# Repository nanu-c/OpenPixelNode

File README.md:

OpenPixelNode
=============

This project includes both hardware and software for an open-source LED controller for up to 4 ArtNet universes.

More images here: http://flic.kr/s/aHsjQY2NrD

Hardware
--------
The hardware design is Arduino-compatible in terms of being based on an ATmega328 microcontroller running at 16MHz.
It uses the Wiznet Wiz820io addon board for Ethernet communication. There are voltage regulators for both 5V and 3.3V for the two logic circuits. This allows the board to be supplied with voltages of 5V to 30V.
There are 4 LED outputs with two digital ports each. This allows the board to control either SPI or single-wire LED strips.
At the moment there is only ICSP headers for programming.

Software
--------
The software is an Arduino sketch using a library for the ArtNet protocol and whatever LED communication protocol you may want to use. Please update the FastLED controller type to whatever LED you are using.

Dependencies
------------
[Arduino_ArtNet](https://github.com/media-architecture/Arduino_ArtNet)

[FastLED](https://github.com/media-architecture/FastLED)

[WIZ_Ethernet_Library](https://github.com/media-architecture/WIZ_Ethernet_Library)

[TrueRandom](https://code.google.com/p/tinkerit/wiki/TrueRandom)

Version history
---------------

### Prototype 2 (January 2014)
### Prototype 1 (September 2013)

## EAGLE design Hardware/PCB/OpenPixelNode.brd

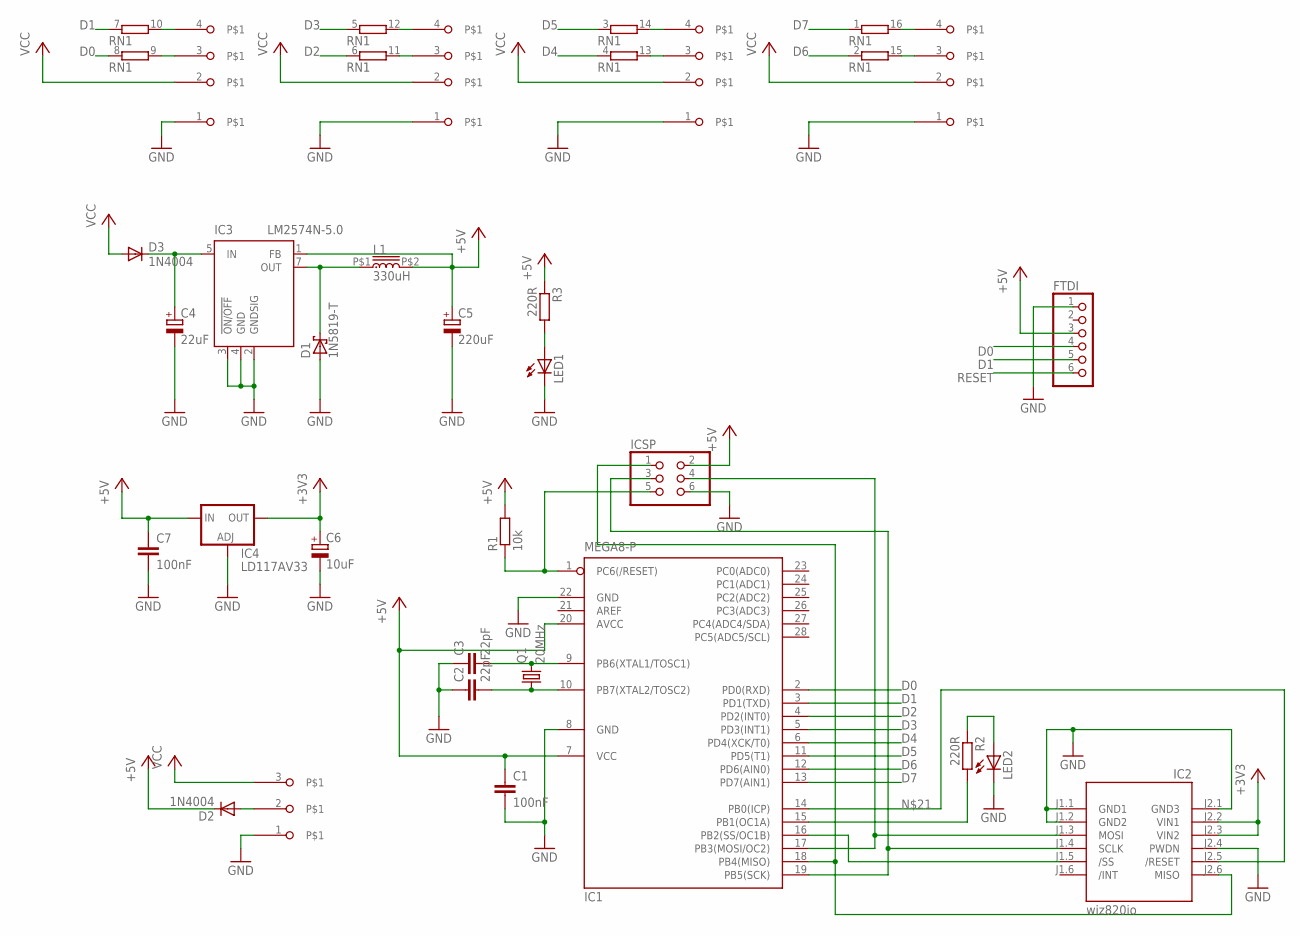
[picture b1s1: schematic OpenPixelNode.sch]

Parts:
C1, C7: 100nF; C025-025X050
C2, C3: 22pF; C025-025X050
C4: 22uF; E2,5-6
C5: 220uF; E2,5-6
C6: 10uF; E2,5-6
D1: 1N5819-T; DO41-7.6
D2, D3: 1N4004; DO41-10
FTDI: PINHD-1X6; 1X06
IC1: MEGA8-P; DIL28-3
IC2: wiz820io; WIZ820IO
IC3: LM2574N-5.0; DIL08
IC4: LD117AV33; TO220L1
ICSP: PINHD-2X3; 2X03
L1: 330uH; 13R334C
LED1, LED2: LED3MM
Q1: 20MHz; HC49/S
R1: 10k; 0207/10
R2, R3: 220R; 0207/10
RN1: 8R-P; DIL16
U$1, U$2, U$3, U$4: 691322110004
U$5: CTB9358/3

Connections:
+3V3: C6.+, IC2.J2.2 (VIN1), IC2.J2.3 (VIN2), IC4.2 (OUT)
+5V: C1.1, C5.+, C7.1, D2.C, FTDI.3, IC1.7 (VCC), IC1.20 (AVCC), IC3.1 (FB), IC4.3 (IN), ICSP.2, L1.P$2 (2), R1.2, R3.1; also elsewhere on the board
D0: FTDI.4, IC1.2 (PD0(RXD)), RN1.8 (1); also elsewhere on the board
D1: FTDI.5, IC1.3 (PD1(TXD)), RN1.7 (1); also elsewhere on the board
D2: IC1.4 (PD2(INT0)), RN1.6 (1)
D3: IC1.5 (PD3(INT1)), RN1.5 (1)
D4: IC1.6 (PD4(XCK/T0)), RN1.4 (1)
D5: IC1.11 (PD5(T1)), RN1.3 (1)
D6: IC1.12 (PD6(AIN0)), RN1.2 (1)
D7: IC1.13 (PD7(AIN1)), RN1.1
GND: C1.2, C2.1, C3.1, C4.-, C5.-, C6.-, C7.2, D1.A, FTDI.1, IC1.8 (GND), IC1.22 (GND), IC2.J1.1 (GND1), IC2.J1.2 (GND2), IC2.J2.1 (GND3), IC2.J2.4 (PWDN), IC3.2 (GNDSIG), IC3.3 (!ON/OFF), IC3.4 (GND), IC4.1 (ADJ), ICSP.6, LED1.K (C), LED2.K (C), U$1.1, U$2.1, U$3.1, U$4.1, U$5.1; also elsewhere on the board
unnamed: LED1.A, R3.2
unnamed: C3.2, IC1.9 (PB6(XTAL1/TOSC1)), Q1.2
unnamed: C2.2, IC1.10 (PB7(XTAL2/TOSC2)), Q1.1
unnamed: IC1.16 (PB2(SS/OC1B)), IC2.J1.5 (/SS)
unnamed: IC1.18 (PB4(MISO)), IC2.J2.6 (MISO), ICSP.1
unnamed: D2.A, U$5.2
unnamed: IC1.17 (PB3(MOSI/OC2)), IC2.J1.3 (MOSI), ICSP.4
unnamed: LED2.A, R2.1
unnamed: C4.+, D3.C, IC3.5 (IN)
unnamed: D1.C, IC3.7 (OUT), L1.P$1 (1)
unnamed: RN1.11 (2), U$2.3
unnamed: RN1.12 (2), U$2.4
unnamed: RN1.13 (2), U$3.3
unnamed: RN1.14 (2), U$3.4
unnamed: RN1.15 (2), U$4.3
unnamed: RN1.16 (2), U$4.4
unnamed: RN1.10 (2), U$1.4
unnamed: RN1.9 (2), U$1.3
unnamed: IC1.14 (PB0(ICP)), IC2.J2.5 (/RESET)
unnamed: IC1.15 (PB1(OC1A)), R2.2
RESET: FTDI.6, IC1.1 (PC6(/RESET)), ICSP.5, R1.1; also elsewhere on the board
SCK: IC1.19 (PB5(SCK)), IC2.J1.4 (SCLK), ICSP.3
VCC: D3.A, U$1.2, U$2.2, U$3.2, U$4.2, U$5.3

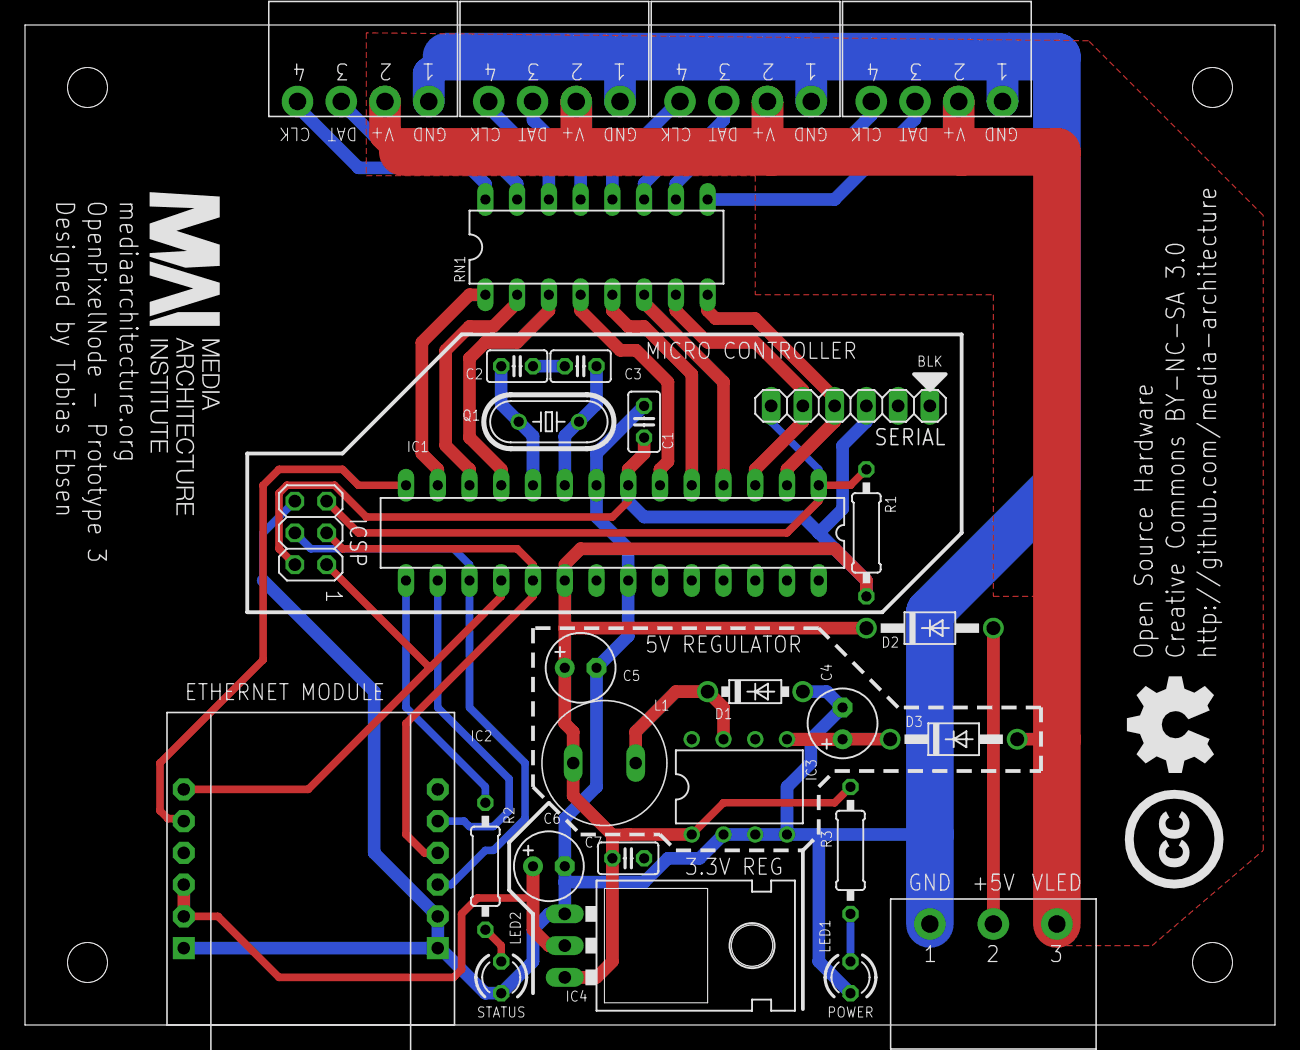
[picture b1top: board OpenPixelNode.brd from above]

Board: 2 copper layers, 100.0 x 80.0 mm, 29 parts (0 on the bottom side), 34 nets.

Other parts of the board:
SERIAL: 1X06

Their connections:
+5V: SERIAL.3; also elsewhere on the board
D0: SERIAL.4; also elsewhere on the board
D1: SERIAL.5; also elsewhere on the board
GND: SERIAL.1; also elsewhere on the board
RESET: SERIAL.6; also elsewhere on the board

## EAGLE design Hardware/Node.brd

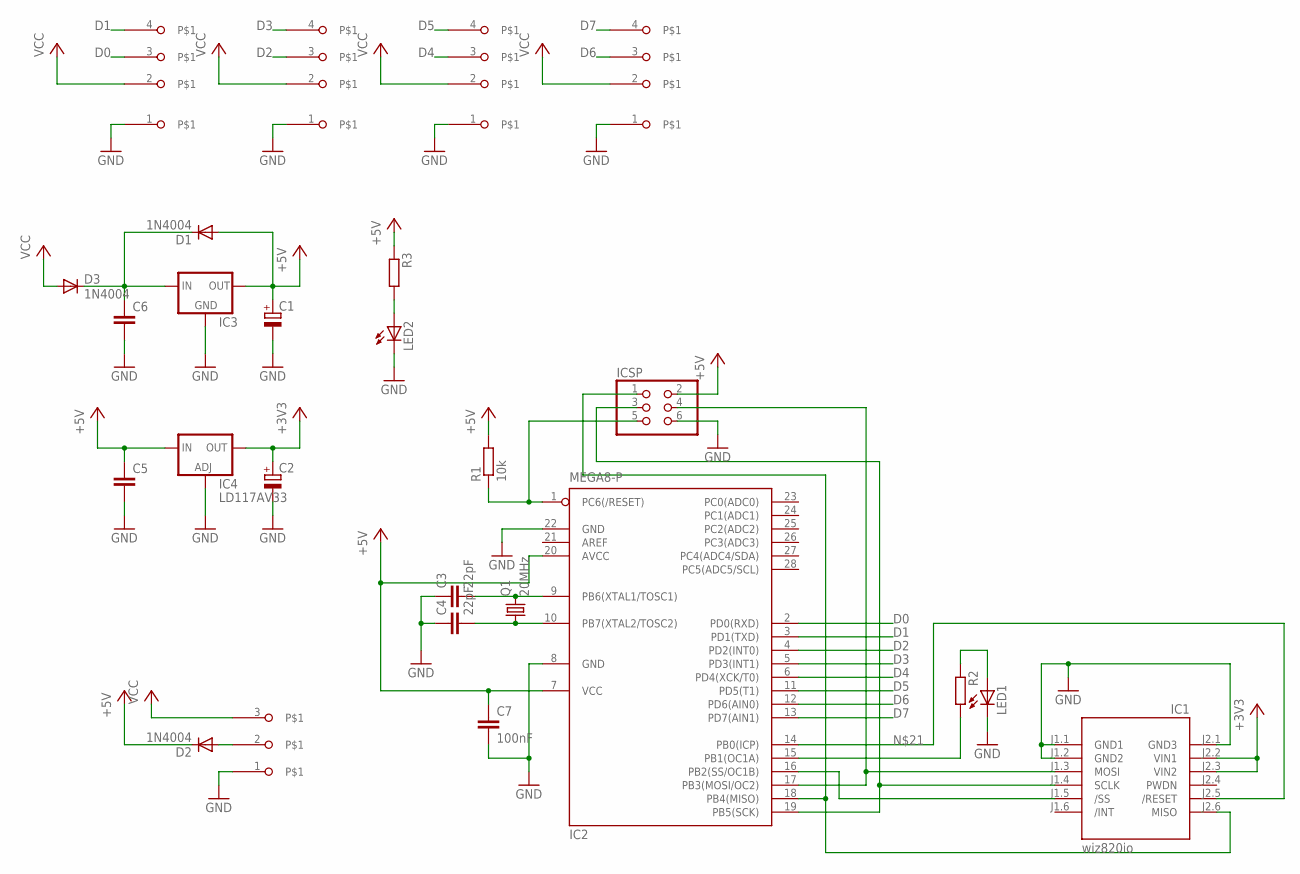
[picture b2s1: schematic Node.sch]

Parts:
C1: CPOL-EUE5-10.5; E5-10,5
C2: CPOL-EUE2.5-6; E2,5-6
C3, C4: 22pF; C025-025X050
C5, C6: C-EU025-025X050; C025-025X050
C7: 100nF; C025-025X050
D1, D2, D3: 1N4004; DO41-10
IC1: wiz820io; WIZ820IO
IC2: MEGA8-P; DIL28-3
IC3: 78XXL
IC4: LD117AV33; TO220L1
ICSP: PINHD-2X3; 2X03
LED1, LED2: LED3MM
Q1: 20MHz; HC49/S
R1: 10k; 0207/10
R2, R3: R-EU_0207/10; 0207/10
U$1, U$2, U$3, U$4: 691322110004
U$5: CTB9358/3

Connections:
+3V3: C2.+, IC1.J2.2 (VIN1), IC1.J2.3 (VIN2), IC4.2 (OUT)
+5V: C1.+, C5.1, C7.1, D1.A, D2.C, IC2.7 (VCC), IC2.20 (AVCC), IC3.OUT, IC4.3 (IN), ICSP.2, R1.2, R3.1
D0: IC2.2 (PD0(RXD)), U$1.3
D1: IC2.3 (PD1(TXD)), U$1.4
D2: IC2.4 (PD2(INT0)), U$2.3
D3: IC2.5 (PD3(INT1)), U$2.4
D4: IC2.6 (PD4(XCK/T0)), U$3.3
D5: IC2.11 (PD5(T1)), U$3.4
D6: IC2.12 (PD6(AIN0)), U$4.3
D7: IC2.13 (PD7(AIN1)), U$4.4
GND: C1.-, C2.-, C3.1, C4.1, C5.2, C6.2, C7.2, IC1.J1.1 (GND1), IC1.J1.2 (GND2), IC1.J2.1 (GND3), IC2.8 (GND), IC2.22 (GND), IC3.GND, IC4.1 (ADJ), ICSP.6, LED1.K (C), LED2.K (C), U$1.1, U$2.1, U$3.1, U$4.1, U$5.1
unnamed: LED2.A, R3.2
unnamed: C3.2, IC2.9 (PB6(XTAL1/TOSC1)), Q1.2
unnamed: C4.2, IC2.10 (PB7(XTAL2/TOSC2)), Q1.1
unnamed: IC1.J1.5 (/SS), IC2.16 (PB2(SS/OC1B))
unnamed: IC1.J2.6 (MISO), IC2.18 (PB4(MISO)), ICSP.1
unnamed: D2.A, U$5.2
unnamed: IC1.J1.3 (MOSI), IC2.17 (PB3(MOSI/OC2)), ICSP.4
unnamed: LED1.A, R2.1
unnamed: C6.1, D1.C, D3.C, IC3.IN
unnamed: IC1.J2.5 (/RESET), IC2.14 (PB0(ICP))
unnamed: IC2.15 (PB1(OC1A)), R2.2
RESET: IC2.1 (PC6(/RESET)), ICSP.5, R1.1
SCK: IC1.J1.4 (SCLK), IC2.19 (PB5(SCK)), ICSP.3
VCC: D3.A, U$1.2, U$2.2, U$3.2, U$4.2, U$5.3

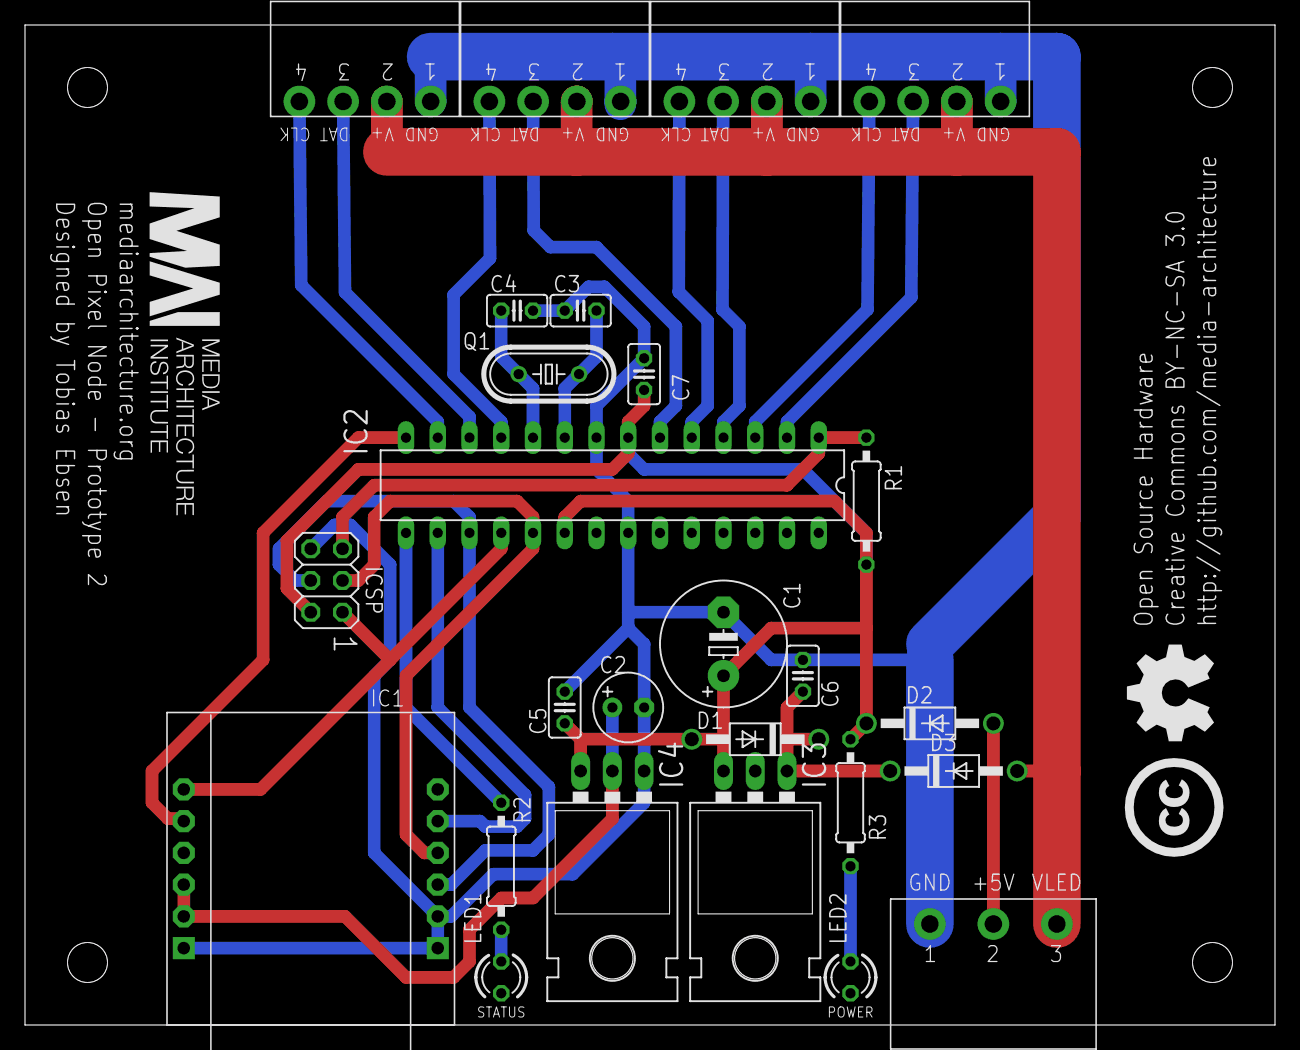
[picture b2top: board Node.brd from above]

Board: 2 copper layers, 100.0 x 80.0 mm, 26 parts (0 on the bottom side), 25 nets.

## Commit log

2014-01-20 Updated dependencies in README
2014-01-20 Updated hardware for prototype 2
2014-02-12 Updated software to support changes in ArtNet library and use FastLED
2014-02-13 Added licenses
2014-02-13 Simplified the software
2014-02-13 Fixed type-o
2014-02-13 Optimized memory size for 360 pixels
2014-02-14 Fixed missing init on FastLED
2014-02-14 Fixed number of pixels error
2014-03-19 Bugfixes and updates for DHCP
2014-03-31 Cleaned up code
2014-04-24 Updated hardware to Prototype 3
2014-04-28 Bugfixes and added watchdog timer

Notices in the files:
Hardware/Node.brd:
Creative Commons BY-NC-SA 3.0
